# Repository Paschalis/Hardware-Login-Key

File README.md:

# 🔐 Hardware Login Key

<p align="center">
  <br/>

</p>

<p align="center">
  <b>Press or tap to auto-type your password suffix — the full password never exists in one place.</b><br/>
  <sub><i>The prefix stays in your mind, the suffix lives in your hand.</i></sub>
</p>

## Introduction

This project offers a straightforward solution for reducing password exposure when logging into a system or website. By pressing a physical button (or touching a capacitive pad) connected to an ATtiny85 microcontroller, the device automatically types a pre-stored password suffix, completing the login without exposing the full credential to observers.

<p align="center">
Pressing the tactile switch on the breadboard prototype sends a keystroke that appears in the terminal.
</p>

## 🎯 Purpose

The aim is to provide a practical alternative to manually typing long or complex passwords in environments where shoulder surfing or observation is a risk. The key injects only a suffix. The prefix stays in the user's memory, so physical possession of the device alone is not enough to authenticate.

## Benefits

- **Reduced exposure** — the full password is never typed in one place or stored in one location
- **Convenience** — complex suffixes are entered automatically with a button press
- **Privacy** — reduces shoulder surfing risk in public or shared environments
- **Portability** — a USB key fits on a keyring and works on any host

## ⚠️ Security Model & Limitations

This device is a **convenience tool**, not a cryptographic security device.

**What it protects against:** shoulder surfing and partial credential capture.

**What it does NOT protect against:**
- **Flash extraction** — the suffix is stored as **plaintext** in ATtiny85 flash
  memory. An attacker with physical access and a standard programmer can dump it
  in under a minute with AVRDUDE. There is no encryption, no secure boot, and no
  hardware protection on the ATtiny85.
- **Compromised host** — keystroke injection via USB HID is visible to any
  software-level keylogger running on the host.

> [!WARNING]
> The ATtiny85 has no hardware security primitives. This device is appropriate for personal, low-threat scenarios. For threat models involving physical access by a motivated attacker, a device with secure boot and encrypted storage is required.
>
>See [SECURITY.md](SECURITY.md) for the full threat model.

## How it Works
The hardware key utilizes an ATtiny85 microcontroller with the V-USB library to implement USB Human Interface Device (HID) keyboard functionality. This allows the ATtiny85 to act as a keyboard when connected to a computer via USB. When the button connected to the ATtiny85 is triggered, it injects a pre-stored password suffix followed by Enter.

<p align="center">
Sequence: (1) user types the prefix, (2) user triggers the device (tactile button or
TTP223), and (3) the ATtiny85 injects suffix + Enter via USB HID. The host concatenates the
parts to form the full credential.
</p>

<p align="center">
From code to reality! The ATtiny85 Hardware Login Key project and its various prototypes. What started as a simple idea is now a fully functional set of secure login devices.
</p>

## Firmware Variants

| Variant | Trigger | Folder |
|---|---|---|
| Tactile switch | Push button on PB1 (active-low, internal pull-up) | `C_implementation/tactile_switch/` |
| Touch pad | TTP223 capacitive sensor on PB1 (active-high) | `C_implementation/touch_pad/` |

Both variants share the same V-USB HID keyboard implementation and the same two-piece password concept.

## Compilation Instructions

> [!TIP]
> **First time working with the ATtiny85?**
> 
> Before diving into this project, it's highly recommended to test your hardware setup and compilation process with a simpler program. The **[ATtiny85_Simple_Code_Test](ATtiny85_Simple_Code_Test/README.md)** project is a perfect "Hello, World!" for your hardware. It plays music through a speaker and confirms that your ATtiny85, programmer, and toolchain are all working correctly before you tackle the more complex V-USB library.

You can modify the permissions of `/dev/ttyACM0` to facilitate communication with your serial device. For detailed instructions, [click here](modify_permissions.md).

> [!IMPORTANT]
> **One-Time Fuse Setup for External Crystal**
> 
> The ATtiny85 must be configured to use the external 16MHz crystal. This is done by setting its "fuse bits." This is a **one-time operation** for each chip. Run this once on each fresh chip.
> 
> 1.  Connect your programmer to the ATtiny85.
> 2.  Run the following command to set the fuses for a 16MHz external crystal:
>     ```bash
>     avrdude -c avrisp -p attiny85 -P /dev/ttyACM0 -b 19200 -U lfuse:w:0xFF:m -U hfuse:w:0xDD:m
>     ```
>
> `lfuse 0xFF` selects the external crystal (8–16 MHz, full swing, maximum startup delay). `hfuse 0xDD` enables SPI programming, keeps the RESET pin active, and enables the Brown-Out Detector at 2.7 V — which prevents the chip from executing with an unstable supply during USB plug/unplug events.
>
> ### How to Revert to the Internal Oscillator
> If you later wish to use this ATtiny85 for a different project that does not require an external crystal, you can revert it to use its internal 8MHz oscillator.
> 
> To revert to the internal 8 MHz oscillator (no crystal needed), run the following command:
> ```bash
> avrdude -c avrisp -p attiny85 -P /dev/ttyACM0 -b 19200 -U lfuse:w:0xE2:m -U hfuse:w:0xDF:m
> ```
> This restores the chip to use its internal 8MHz clock source, which is a common setting for many projects (like the `ATtiny85_Simple_Code_Test`).
>
 
> [!WARNING]
> Be extremely careful when setting fuses. Incorrect fuse values can prevent the chip from being reprogrammed via ISP. Always verify values before running the command. Use https://www.engbedded.com/fusecalc/ to double-check.

Install the toolchain:

```bash
# Linux
sudo apt-get install make gcc-avr binutils-avr avr-libc avrdude

# macOS
brew tap osx-cross/avr && brew install avr-gcc avrdude
```

Build and flash (from inside a variant folder):

```bash
cd C_implementation/tactile_switch    # or touch_pad
make          # compile
make upload   # flash via Arduino-as-ISP
```

For detailed programmer wiring, port configuration, and manual build reference, see [INSTRUCTIONS_C.md](INSTRUCTIONS_C.md) and [C_Makefile_Instructions.md](C_Makefile_Instructions.md).

## 📋 Usage — Two-Piece Password

This hardware key uses a **"Two-Piece Password"** approach for enhanced security. The device does not store your full password. Instead, it stores only the complex second half, while you remember and type the simpler first half. This makes the physical key useless if it is ever lost or stolen.

> [!IMPORTANT]
> The device stores only the complex **suffix** of a password. The simpler **prefix** lives in the user's memory. The full credential never exists in a single place.

### The Concept in Action

Let's imagine your full, desired password is: `Key_!#2025_complex`

*   **The part you remember and type first (The Prefix):** `Key_`
*   **The part stored on your hardware key (The Suffix):** `!#2025_complex`

### Login Steps

1.  Navigate to the password field of the login form.
2.  Manually type the first part of your password (e.g., `Key_`).
3.  Plug in your hardware key.
4.  Press the button on the key.
5.  The key will automatically type the complex second half of the password (`!#2025_complex`) and press Enter, logging you in securely.

---

## PCB Designs

### In KiCad

The hardware key is available in multiple PCB package versions to accommodate different assembly preferences:
- **Through-Hole (DIP)**: Easy to hand-solder, ideal for prototyping.
  - 
  *With tactile switch.*
- **SMD (SOIC)**: Compact and solderable by hand with a fine-tip iron.
  - 
  *With tactile switch.*
- **SMD (QFN)**: Smallest footprint with push button.
  - 
    *With tactile switch.*

  - 
    **QFN PCB designed for a touch pad using the TTP223 IC for enhanced reliability.**  
    - Uses a simple high/low output for touch detection, similar to a tactile switch, providing a straightforward 0 or 1 output.  
    - The PCB is designed with **4 layers** to optimize signal integrity and reliability.

## 🛒 Requirements

### Through-Hole (DIP)

| Reference | Value | Footprint | Qty |
|---|---|---|---|
| C1, C2 | 22 pF | C_Disc_D5.0mm_W2.5mm_P5.00mm | 2 |
| C3 | 100 nF | C_Disc_D5.0mm_W2.5mm_P5.00mm | 1 |
| C4 | 10 µF | CP_Radial_D4.0mm_P2.00mm | 1 |
| D1, D2 | 3V6 Zener | D_DO-15_P10.16mm_Horizontal | 2 |
| J1 | USB-AM-S-X-X-TH | SAMTEC_USB-AM-S-X-X-TH | 1 |
| J2 | Conn 1×06 | Molex_PicoBlade_53047-0610 | 1 |
| R1, R2 | 68 Ω | R_Axial_DIN0204_P5.08mm | 2 |
| R3 | 10 kΩ | R_Axial_DIN0204_P5.08mm | 1 |
| R4 | 1.5 kΩ | R_Axial_DIN0204_P5.08mm | 1 |
| S1 | B3F-1000 | SW_B3F-1000 | 1 |
| U1 | ATtiny85-20P | DIP-8_W7.62mm | 1 |
| Y1 | 16 MHz | Crystal_HC49-4H_Vertical | 1 |

<p align="center">
  <b>DIP 3D render of the hardware login key’s PCB using the Through-Hole (DIP) package in KiCad</b>
</p>

### SMD — SOIC-8

| Reference | Value | Footprint | Qty |
|---|---|---|---|
| C1 | 100 nF | C_0603_HandSolder | 1 |
| C2, C3 | 22 pF | C_0603_HandSolder | 2 |
| C4 | 10 µF | C_0805_HandSolder | 1 |
| D1, D2 | 3V6 Zener | D_0603_HandSolder | 2 |
| J1 | USB-AM-S-X-X-TH | USB_PCB | 1 |
| J2 | Conn 1×06 | JST_SH_SM06B-SRSS-TB | 1 |
| R1, R2 | 68 Ω | R_0603_HandSolder | 2 |
| R3 | 1.5 kΩ | R_0603_HandSolder | 1 |
| R5 | 10 kΩ | R_0603_HandSolder | 1 |
| S2 | PTS525SM15SMTR2LFS | SW_PTS525SM15SMTR2LFS | 1 |
| U1 | ATtiny85-20P | SOIC-8_5.3x5.3mm | 1 |
| Y2 | 16 MHz | Crystal_SMD_3225-4Pin | 1 |

<p align="center">
  <b>3D model of the hardware login key’s PCB using the SMD (SOIC) package in KiCad.</b>
</p>

### SMD — QFN-20 with tactile switch

| Reference | Value | Footprint | Qty |
|---|---|---|---|
| C1 | 100 nF | C_0603_HandSolder | 1 |
| C2, C3 | 22 pF | C_0603_HandSolder | 2 |
| C4 | 10 µF | C_0805_HandSolder | 1 |
| D1, D2 | 3V6 Zener | D_0603_HandSolder | 2 |
| J1 | USB-AM-S-X-X-TH | USB_PCB | 1 |
| J2 | Conn 1×06 | JST_SH_SM06B-SRSS-TB | 1 |
| R1, R2 | 68 Ω | R_0603_HandSolder | 2 |
| R3 | 1.5 kΩ | R_0603_HandSolder | 1 |
| R5 | 10 kΩ | R_0603_HandSolder | 1 |
| S2 | PTS525SM15SMTR2LFS | SW_PTS525SM15SMTR2LFS | 1 |
| U1 | ATtiny85-20M | QFN-20-1EP_4x4mm | 1 |
| Y2 | 16 MHz | Crystal_SMD_3225-4Pin | 1 |

<p align="center">
  <b>3D model of the hardware login key’s PCB using the QFN package in KiCad.</b>
</p>

### SMD — QFN-20 with TTP223 capacitive touch (4-layer PCB) and Reversible USB Functionality

| Reference | Value | Footprint | Qty |
|---|---|---|---|
| C1 | 100 nF | C_0603_HandSolder | 1 |
| C2, C3 | 22 pF | C_0603_HandSolder | 2 |
| C4 | 1 µF | C_0603_HandSolder | 1 |
| C5 | 30 pF | C_0603_HandSolder | 1 |
| C6 | 10 µF | C_0805_HandSolder | 1 |
| D1, D2 | 3V6 Zener | D_0603_HandSolder | 2 |
| J1 | USB-AM-S-X-X-TH | USB_PCB | 1 |
| J2 | M50-3930642 | HARWIN_M50-3930642 | 1 |
| R1, R2 | 68 Ω | R_0603_HandSolder | 2 |
| R3 | 1.5 kΩ | R_0603_HandSolder | 1 |
| R5 | 10 kΩ | R_0603_HandSolder | 1 |
| TP1, TP2 | Test point | TestPoint_Pad_D3.0mm | 2 |
| U1 | ATtiny85-20M | QFN-20-1EP_4x4mm | 1 |
| U2 | TTP223-BA6 | SOT23-6 | 1 |
| Y2 | 16 MHz | Crystal_SMD_3225-4Pin | 1 |

<p align="center">
  <b>3D model of the hardware login key’s PCB using the QFN package in KiCad.</b> 
  <br> 
  With the TTP223 IC. (Uses simple high/low output for touch detection, similar to a tactile switch, with default code for straightforward 0 or 1 output.)
</p>

## 🏗️ 3D Printed Enclosure

A 3D printed case is available for the hardware key. To use it, follow these steps:
1. Open the `3d_printed_case` folder.
2. Load the `hardware_key_case.stl` file into your 3D printer software.
3. Print the case using your 3D printer.
4. Once printed, assemble the hardware key inside the case for added protection and aesthetics.

## 📄 System Requirements Specification

<p align="center">
  <b>Click the image to open the full SRS (PDF).</b>
</p>

## 🧑‍💻 Authors
-  

## 👥 Contributors
-
-
-
-

## 🙏 Acknowledgements

This project stands on the shoulders of giants. A special thank you to the developers and communities behind these essential open-source tools:

*   **V-USB:** The core USB functionality of this hardware key is made possible by the V-USB library, a firmware-only USB driver for AVR microcontrollers from [Objective Development](https://www.obdev.at/vusb/).
*   **KiCad:** All PCB designs were created using KiCad, a powerful, free, and open-source electronics design automation (EDA) suite. Learn more at the [KiCad website](https://www.kicad.org/).

## 📜 License

This project is licensed under the [GPLv3 License](https://opensource.org/licenses/GPL-3.0) - see the [LICENSE](LICENSE) file for details.

- 

**Thank you for visiting Hardware-Login-Key!** 🔐✨

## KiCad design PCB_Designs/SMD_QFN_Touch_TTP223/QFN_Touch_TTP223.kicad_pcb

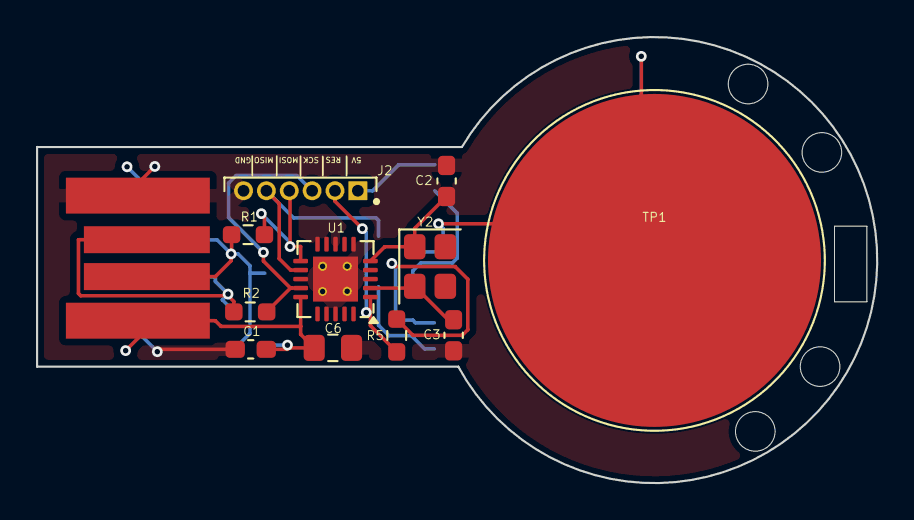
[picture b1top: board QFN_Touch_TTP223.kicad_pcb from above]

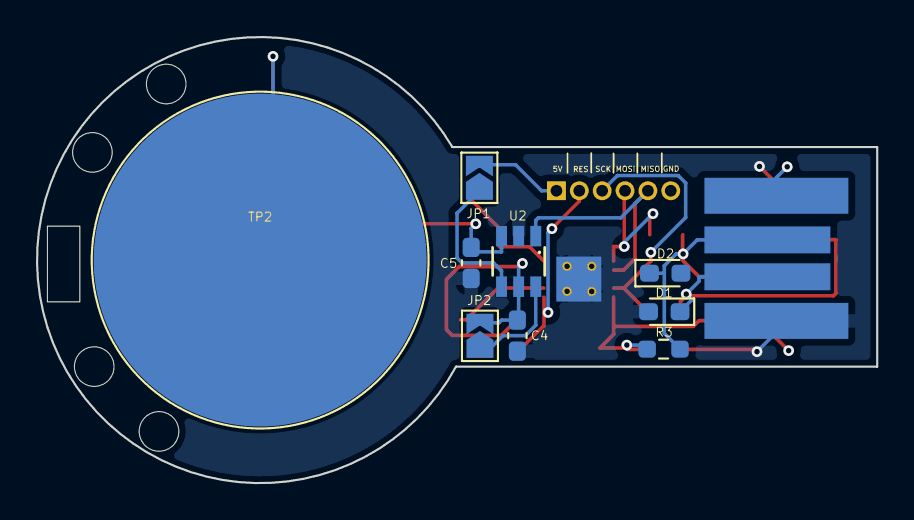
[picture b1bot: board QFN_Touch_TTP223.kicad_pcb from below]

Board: 4 copper layers, 46.7 x 24.8 mm, 22 parts (10 on the bottom side), 13 nets.

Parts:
C1: 100nF; C_0603_1608Metric_Pad1.08x0.95mm_HandSolder
C2, C3: 22pF; C_0603_1608Metric_Pad1.08x0.95mm_HandSolder
C4: 1uF; C_0603_1608Metric_Pad1.08x0.95mm_HandSolder
C5: 30pF; C_0603_1608Metric_Pad1.08x0.95mm_HandSolder
C6: 10μF; C_0805_2012Metric_Pad1.18x1.45mm_HandSolder
D1, D2: 3V6; D_0603_1608Metric_Pad1.05x0.95mm_HandSolder
J1, J5: USB-AM-S-X-X-TH; USB_PCB
J2: M50-3930642; HARWIN_M50-3930642
JP1, JP2: SolderJumper_2_Open; SolderJumper-2_P1.3mm_Open_TrianglePad1.0x1.5mm
R1, R2: 68R; R_0603_1608Metric_Pad0.98x0.95mm_HandSolder
R3: 1k5; R_0603_1608Metric_Pad0.98x0.95mm_HandSolder
R5: 10k; R_0603_1608Metric_Pad0.98x0.95mm_HandSolder
TP1, TP2: TestPoint; TestPoint_Pad_D3.0mm
U1: ATtiny85-20M; QFN-20-1EP_4x4mm_P0.5mm_EP2.5x2.5mm_ThermalVias
U2: TTP223-BA6; SOT23-6
Y2: 16MHz; Crystal_SMD_3225-4Pin_3.2x2.5mm

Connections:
+5V: C1.1, C4.1, C6.1, J1.01 (VCC), J2.1, J5.01 (VCC), JP1.2 (B), JP2.2 (B), R3.1, R5.1, U1.15 (VCC), U2.5 (VDD)
/Data+: J2.3, R2.2, U1.14 (PB2)
/Data-: J2.4, R1.2, U1.11 (AREF/PB0)
/MISO: J2.5, U1.12 (PB1), U2.1 (Q)
/RESET: J2.2, R5.2, U1.1 (~RESET/PB5)
/XTAL1: C3.1, U1.2 (XTAL1/PB3), Y2.2
/XTAL2: C2.1, U1.5 (XTAL2/PB4), Y2.1
GND: C1.2, C2.2, C3.2, C4.2, C5.2, C6.2, D1.2 (A), D2.2 (A), J1.04 (GND), J2.6, J5.04 (GND), U1.8 (GND), U1.21 (GND), U2.2 (VSS)
unnamed: D1.1 (K), J1.03 (D+), J5.03 (D+), R2.1
unnamed: D2.1 (K), J1.02 (D-), J5.02 (D-), R1.1, R3.2
unnamed: JP1.1 (A), U2.4 (AHLB)
unnamed: JP2.1 (A), U2.6 (TOG)
unnamed: C5.1, TP1.1, TP2.1, U2.3 (I)

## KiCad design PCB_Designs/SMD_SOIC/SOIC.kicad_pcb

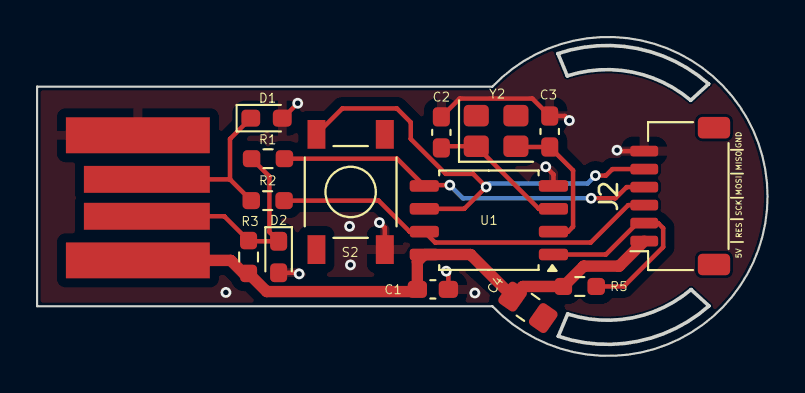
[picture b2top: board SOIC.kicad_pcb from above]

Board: 2 copper layers, 40.5 x 17.6 mm, 15 parts (0 on the bottom side), 10 nets.

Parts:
C1: 100nF; C_0603_1608Metric_Pad1.08x0.95mm_HandSolder
C2, C3: 22pF; C_0603_1608Metric_Pad1.08x0.95mm_HandSolder
C4: 10μF; C_0805_2012Metric_Pad1.18x1.45mm_HandSolder
D1, D2: 3V6; D_0603_1608Metric_Pad1.05x0.95mm_HandSolder
J1: USB-AM-S-X-X-TH; USB_PCB
J2: Conn_01x06_Pin; JST_SH_SM06B-SRSS-TB_1x06-1MP_P1.00mm_Horizontal
R1, R2: 68R; R_0603_1608Metric_Pad0.98x0.95mm_HandSolder
R3: 1k5; R_0603_1608Metric_Pad0.98x0.95mm_HandSolder
R5: 10k; R_0603_1608Metric_Pad0.98x0.95mm_HandSolder
S2: PTS525SM15SMTR2LFS; SW_PTS525SM15SMTR2LFS
U1: ATtiny85-20P; SOIC-8_5.3x5.3mm_P1.27mm
Y2: 16MHz; Crystal_SMD_3225-4Pin_3.2x2.5mm

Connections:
+5V: C1.1, C4.1, J1.01 (VCC), J2.1, R3.1, R5.1, U1.8 (VCC)
/Data+: J2.3, R2.2, U1.7 (PB2)
/Data-: J2.4, R1.2, U1.5 (AREF/PB0)
/MISO: J2.5, S2.2, U1.6 (PB1)
/RESET: J2.2, R5.2, U1.1 (~RESET/PB5)
/XTAL1: C3.1, U1.2 (XTAL1/PB3), Y2.2
/XTAL2: C2.1, U1.3 (XTAL2/PB4), Y2.1
GND: C1.2, C2.2, C3.2, C4.2, D1.2 (A), D2.2 (A), J1.04 (GND), J2.6, S2.3, U1.4 (GND)
unnamed: D1.1 (K), J1.03 (D+), R2.1
unnamed: D2.1 (K), J1.02 (D-), R1.1, R3.2

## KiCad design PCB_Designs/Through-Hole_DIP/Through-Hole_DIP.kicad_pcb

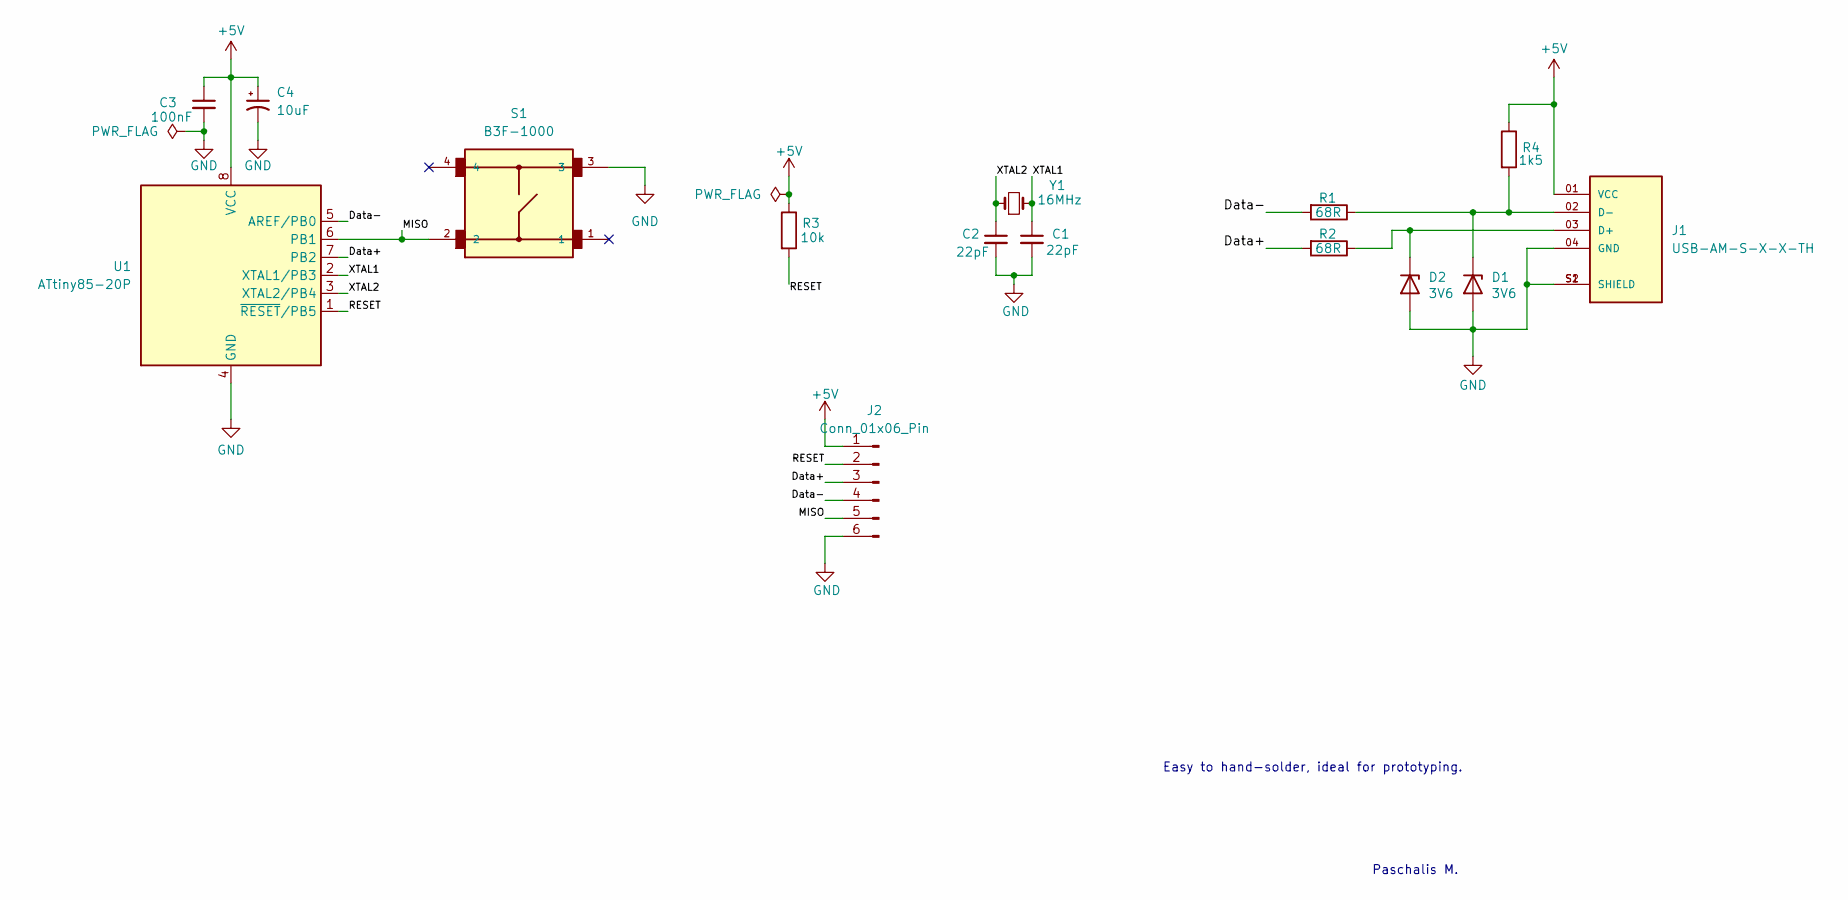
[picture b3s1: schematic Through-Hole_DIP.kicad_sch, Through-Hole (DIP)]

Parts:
C1, C2: 22pF; C_Disc_D5.0mm_W2.5mm_P5.00mm
C3: 100nF; C_Disc_D5.0mm_W2.5mm_P5.00mm
C4: 10uF; CP_Radial_D4.0mm_P2.00mm
D1, D2: 3V6; D_DO-15_P10.16mm_Horizontal
J1: USB-AM-S-X-X-TH; SAMTEC_USB-AM-S-X-X-TH; PARTREV U
J2: Conn_01x06_Pin; Molex_PicoBlade_53047-0610_1x06_P1.25mm_Vertical
R1, R2: 68R; R_Axial_DIN0204_L3.6mm_D1.6mm_P5.08mm_Horizontal
R3: 10k; R_Axial_DIN0204_L3.6mm_D1.6mm_P5.08mm_Horizontal
R4: 1k5; R_Axial_DIN0204_L3.6mm_D1.6mm_P5.08mm_Horizontal
S1: B3F-1000; SW_B3F-1000
U1: ATtiny85-20P; DIP-8_W7.62mm
Y1: 16MHz; Crystal_HC49-4H_Vertical

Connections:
+5V: C3.1, C4.1, J1.01 (VCC), J2.1, R3.1, R4.1, U1.8 (VCC)
/Data+: J2.3, R2.2, U1.7 (PB2)
/Data-: J2.4, R1.2, U1.5 (AREF/PB0)
/MISO: J2.5, S1.2, U1.6 (PB1)
/RESET: J2.2, R3.2, U1.1 (~RESET/PB5)
/XTAL1: C1.1, U1.2 (XTAL1/PB3), Y1.2
/XTAL2: C2.1, U1.3 (XTAL2/PB4), Y1.1
GND: C1.2, C2.2, C3.2, C4.2, D1.2 (A), D2.2 (A), J1.04 (GND), J1.S1 (SHIELD), J1.S2 (SHIELD), J2.6, S1.3, U1.4 (GND)
unnamed: D1.1 (K), J1.02 (D-), R1.1, R4.2
unnamed: D2.1 (K), J1.03 (D+), R2.1

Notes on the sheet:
Paschalis M.
Easy to hand-solder, ideal for prototyping.

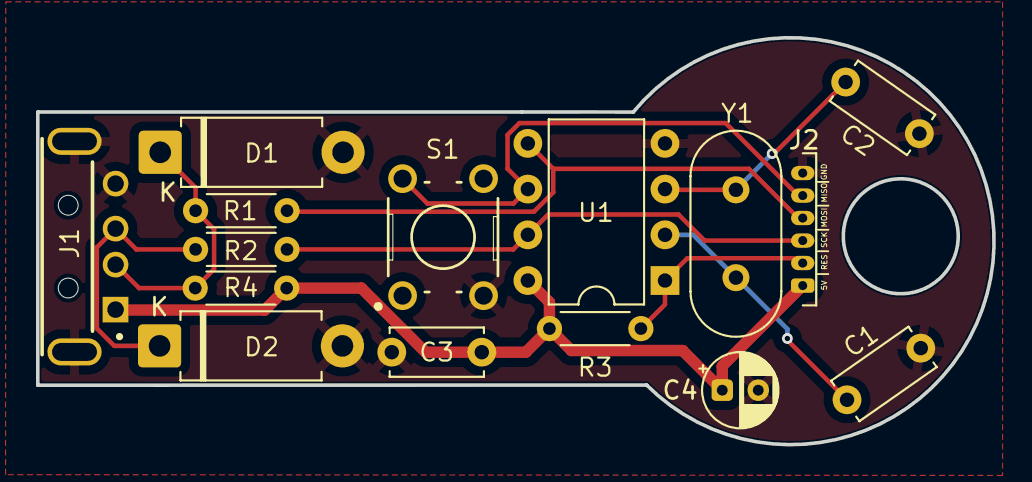
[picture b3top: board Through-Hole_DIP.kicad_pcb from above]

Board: 2 copper layers, 53.1 x 22.6 mm, 15 parts (0 on the bottom side), 10 nets.

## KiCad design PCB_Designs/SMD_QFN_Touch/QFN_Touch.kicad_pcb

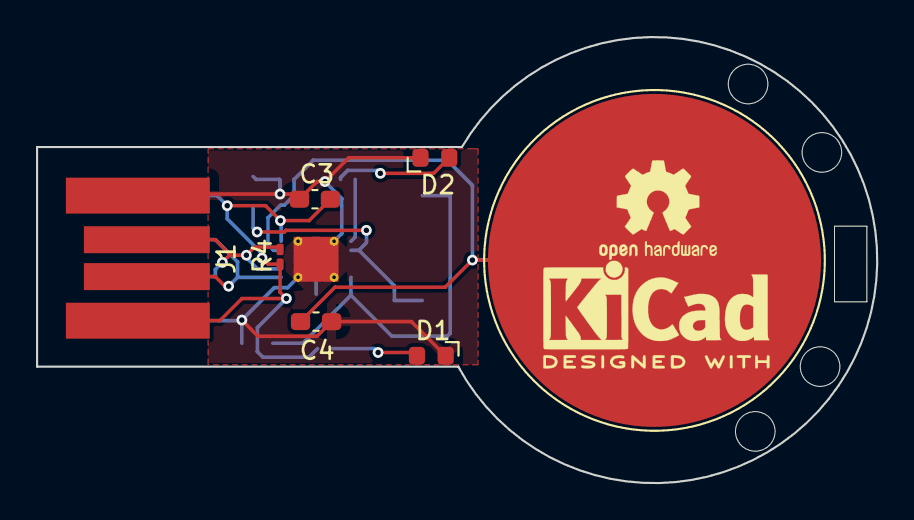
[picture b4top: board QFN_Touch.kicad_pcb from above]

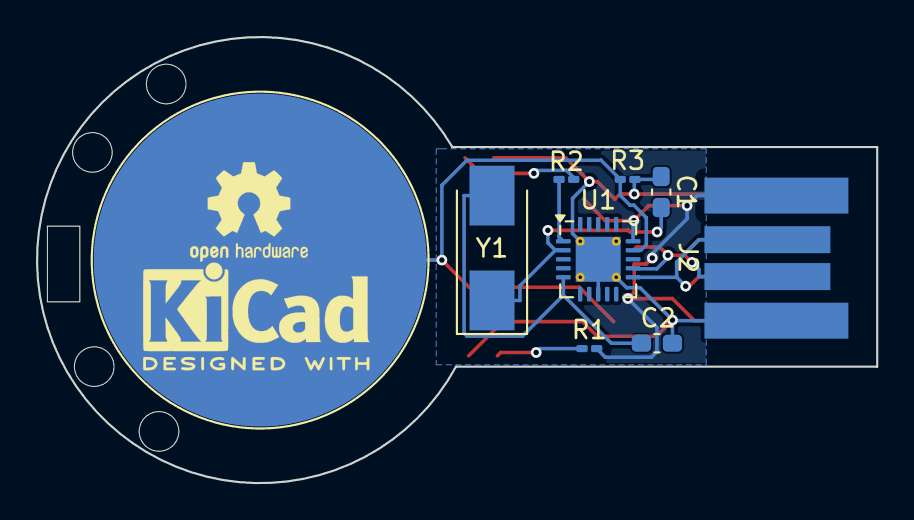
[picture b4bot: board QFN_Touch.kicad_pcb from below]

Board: 2 copper layers, 46.7 x 24.8 mm, 20 parts (11 on the bottom side), 10 nets.

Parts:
BacnKi: KiCad-Logo2_5mm_SilkScreen
C1, C2: 22pF; C_0603_1608Metric_Pad1.08x0.95mm_HandSolder
C3: 0.1uF; C_0603_1608Metric_Pad1.08x0.95mm_HandSolder
C4: 10uF; C_0603_1608Metric_Pad1.08x0.95mm_HandSolder
D1: LED RED; LED_Kingbright_APA1606_1.6x0.6mm_Horizontal_NEW
D2: LED GREEN; LED_Kingbright_APA1606_1.6x0.6mm_Horizontal_NEW
Front: OSHW-Logo2_7.3x6mm_SilkScreen
FrontKi: KiCad-Logo2_5mm_SilkScreen
J1, J2: USB-AM-S-X-X-TH; USB_PCB
R1, R3: 10k; R_0201_0603Metric_Pad0.64x0.40mm_HandSolder
R2: 330; R_0201_0603Metric_Pad0.64x0.40mm_HandSolder
R4: 1k5; R_0201_0603Metric_Pad0.64x0.40mm_HandSolder
TP1, TP2: TestPoint; TestPoint_Pad_D3.0mm
U1: ATtiny85-20M; QFN-20-1EP_4x4mm_P0.5mm_EP2.5x2.5mm_ThermalVias
Y1: 12MHz; Crystal_SMD_0603-2Pin_6.0x3.5mm_HandSoldering
back: OSHW-Logo2_7.3x6mm_SilkScreen

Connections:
+5V: C3.1, J1.01 (VCC), J2.01 (VCC), R1.2, R4.1, U1.15 (VCC)
/Data+: J1.03 (D+), J2.03 (D+), R4.2, U1.12 (PB1)
/Data-: J1.02 (D-), J2.02 (D-), U1.11 (AREF/PB0)
GND: C1.2, C2.2, C3.2, C4.2, D1.1 (K), D2.1 (K), J1.04 (GND), J2.04 (GND), R3.2, U1.8 (GND), U1.21 (GND)
unnamed: D1.2 (A), R1.1
unnamed: D2.2 (A), R2.2
unnamed: C4.1, R3.1, TP1.1, TP2.1, U1.14 (PB2)
unnamed: C1.1, U1.2 (XTAL1/PB3), Y1.1
unnamed: C2.1, U1.5 (XTAL2/PB4), Y1.2
unnamed: R2.1, U1.1 (~RESET/PB5)

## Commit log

2024-04-27 Initial project version: initial commit
2024-04-28 Modified README.md
2024-05-09 Modified INSTRUCTIONS_C.md
2024-05-09 Modified Makefile
2024-05-23 Modified
2024-08-02 Update README with Parts List and PCB Design Details
    - Enhanced the README to include detailed parts lists for both SMD and DIP versions of the hardware login key.
    - Added PCB design sections with images for Through-Hole (DIP), SMD (SOIC), and QFN versions.
    - Updated folder structure to include PCB design files and images.
    - Added links to datasheets for key components.
    - Clarified the usage instructions and requirements for different PCB versions.
    Updated the `Requirements` section with detailed component specifications for SMD and DIP versions, including datasheets and footprints. Incorporated image references for each PCB design in the `PCB_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
2024-08-02 Add KiCad GIF for Schematic and PCB Screenshots
    - Added a GIF demonstrating the KiCad design workflow for the schematic and PCB.
    - Updated `README.md` to include the GIF in the `PCB_Designs` section.
2024-08-02 Modified kicad_workflow.gif
2024-08-07 Reposition LEDs on PCB for 3D enclosure alignment
    Moved LEDs to new positions on the PCB to ensure proper fit and alignment with the 3D enclosure design. This adjustment accommodates the enclosure's dimensions and improves overall integration.
2024-08-11 Fix USB pin definitions for Digispark: swap D+ and D- pins
    - Changed USB_CFG_DMINUS_BIT from 4 to 3
    - Changed USB_CFG_DPLUS_BIT from 3 to 4
    The pin configuration now matches the Digispark pinout for D+ and D-.
2024-08-11 Update README.md with new section titles and image captions
2024-08-11 Add SMD QFN Touch PCB design files to repository
2024-08-11 Add new images for QFN Touch PCB designs
2024-08-20 Update QFN touch pad PCB design files and README
    - Modified KiCad project and schematic files for SMD QFN touch pad using TTP223 IC
    - Deleted unnecessary auto-saved and lock files from the project directory
    - Added images of the QFN Touch PCB design
    - Updated README to include details on the 4-layer PCB design
2024-08-20 Fix license mismatch: Update from MIT to GPLv3
    - Updated LICENSE file to reflect the GPLv3 license.
    - Modified README.md to reference the new GPLv3 license.
2026-04-19 Add C firmware: tactile switch and touch pad variants
    ATtiny85 V-USB HID keyboard firmware implementing the two-piece
    password split concept. Two variants:
    - tactile_switch: active-low push button on PB1, internal pull-up
    - touch_pad: TTP223 capacitive sensor on PB1, active-high
    Both use V-USB for USB HID keyboard enumeration at 16 MHz.
    Flash usage: ~22% of 8 KB (1.86 KB). Also includes the
2026-04-19 Add KiCad PCB designs: DIP, SOIC, QFN, QFN+TTP223 touch
    Four hardware variants in KiCad 7:
    - Through-Hole DIP: hand-solderable, prototyping friendly
    - SMD SOIC-8: compact, hand-solderable
    - SMD QFN-20: minimal footprint, tactile switch
    - SMD QFN-20 + TTP223: capacitive touch, 4-layer PCB for
    improved signal integrity
2026-04-30 Add cleaned SRS.pdf
